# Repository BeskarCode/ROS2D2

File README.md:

# ROS2D2

<picture>
  <source media="(prefers-color-scheme: dark)" srcset="media/ros2d2-logo-dark.png">
  
</picture>

> **Work in progress: everything here is still being tested.** Parts run in the simulator and on
> the bench; testing on the droid is under way. Not yet a recipe to follow on your own droid.

A ROS 2 brain for an R2-D2 that runs ShadowMD. It works with [ShadowMD Lite](https://github.com/BeskarCode/ShadowMDLite) or with the classic Shadow MD ([SHADOW_MD_EEBEL](https://github.com/BeskarCode/SHADOW_MD_EEBEL)); in both it is enabled with `ENABLE_ROS2D2`, off by default. A Raspberry Pi 4 sits on top of the
droid's Arduino Mega: the Pi handles the senses (cameras, voice, later a lidar) and
decides what to do, and the Mega keeps driving the motors, sounds and lights.

The controller always wins: touch the stick and control is back with you at once.
The Mega also stops the dome if the Pi goes quiet for 300 ms.

First demo: the dome turns to look at you. It is the [DomeTracker](https://github.com/BeskarCode/DomeTracker)
proof of concept, split into ROS 2 nodes.

```
 camera ──image_raw──> face detector ──faces──> dome tracker ──/dome/speed_cmd──> Mega bridge ──DM:<speed>──> Mega
```

## The web console

ROS2D2 has its own web console, served by the Pi (`http://<pi>:8080`), to watch and set up the droid
from any browser.
Everything it does, page by page: the **[user manual](MANUAL.md)** ([en castellano](MANUAL_es.md)); its
**Manual** button opens it at the page you are on.

**Navigation**: the floor around R2 seen from above with the lidar's points, the free circle and
each sensor's beam, R2 in 3D, and every sensor's reading. Click the floor to send R2 there.

**Setup → Sensors**: where each sensor sits and what it covers. Drag a test object round R2 and the
sensors that would see it light up; switch a sensor that gives false readings to *ignored* in one
click; set the lidar (motor, scan mode, blind sectors) and read what it says about itself.

**Setup → Modes**: each automatic mode starts with its own controller combination. What each one does:

| | |
|---|---|
|  |  |
|  |  |

## Hardware

What ROS2D2 adds to a ShadowMD droid, how it connects and the bill of materials: [HARDWARE.md](HARDWARE.md).

## Packages (`ros2_ws/src`)

| Package | Node | What it does |
|---|---|---|
| `r2_camera` | `camera_node` | USB or network (ESP32-CAM) camera, one instance per camera |
| `r2_vision` | `face_detector` | OpenCV YuNet face detector, closest face first |
| `r2_dome_tracker` | `dome_tracker` | Dome speed from the face position (control law tuned on the droid) |
| `r2_shadow_bridge` | `mega_bridge`, `foot_calibrate` | The only node that talks to the Mega over USB serial; the feet move only in autonomous mode (PS + L2 on the foot controller), the dome only with face tracking on (PS + L2 on the dome controller); the two are independent |
| `r2_imu` | `imu_node` | MPU6050 gyro and accelerometer over I2C, plus a Madgwick filter |
| `r2_sensors` | `sensor_tf`, `fake_lidar`, `scan_crop`, `lidar_motor` | Where the lidar and the distance sensors (VL53L0X, HC-SR04 on a Pico) sit, from `sensors.yaml` (edited in the web console: Setup → Sensors), on `/tf_static`; the lidar's `/scan` cut to what the droid does not hide; a pretend lidar with `lidar:=sim` |
| `r2_pico_bridge` | `pico_bridge`, `fake_pico` | Talks to the Raspberry Pi Pico that reads the distance sensors (`firmware/r2_pico_sensors`, on `/dev/r2-pico`): sends it the sensors and pins from `sensors.yaml` (again on every save), publishes `/range/<name>` for each sensor that answers and `/pico/state` (JSON) for the console. Not started with `sim:=true` (the simulator has its own `/range`) or `pico:=false`. Flash the Pico from the PC with `firmware/r2_pico_sensors/flash.sh` |
| `r2_web` | `web_console` | Web console on port 8080: cameras, faces, 3D dome, camera and sensor setup |
| `r2_bringup` | | Launch files: `ros2 launch r2_bringup dome_tracker.launch.py` |

## Raspberry Pi setup

Ubuntu Server 24.04 (64-bit) on a Pi 4, then:

```
sudo bash setup/setup_r2_brain.sh
```

It installs ROS 2 Jazzy, the camera and web tools, and the serial port permissions.
Takes 1.5 to 2.5 hours, mostly waiting on the microSD: use a fast A2 card.

From then on, to put the code of this computer on the Pi (Git Bash on the computer):

```
PI=<your-user>@<pi-address> setup/deploy.sh              # every package, or name some: r2_web r2_nav
```

It copies `ros2_ws/src`, rebuilds what it copied and writes `~/r2_ws/VERSION` (the commit),
which the web console shows in Setup -> System.

So that the console can check GitHub for new Pico firmware and flash it (Setup -> System ->
Pico firmware), once, on the Pi as the ROS2D2 user (not root):

```
setup/install_pico_toolchain.sh
```

It installs `arduino-cli` with the Pico core and libraries (about 2 GB, a few minutes), a copy
of the repo's `firmware/` in `~/ros2d2-firmware`, and `/usr/local/sbin/r2-pico-flash` with a
sudoers rule for that one script. A build on a Pi 4 takes 2 to 3 minutes.

### Naming the USB devices (lidar, Mega, Pico)

ROS2D2 finds its USB serial devices by fixed names: `/dev/r2-mega`, `/dev/r2-lidar` and
`/dev/r2-pico`. Genuine Megas and the Pico get theirs on their own. The RPLIDAR C1's USB
adapter uses a common chip (CP210x) that a Mega clone can also have, so it is named by its
serial number, once:

```
./setup/r2-usb-names.sh                       # lists the ports: plug in the lidar and find its line
sudo ./setup/r2-usb-names.sh r2-lidar ttyUSB0 # the device now on ttyUSB0 is /dev/r2-lidar from now on
sudo systemctl restart r2d2
```

With `/dev/r2-lidar` present, the lidar starts with the droid (`lidar:=auto`) and its scan
shows in the web console (Sensors and Navigation). Its driver runs in its own service,
`r2d2-lidar` (installed by `setup_r2_brain.sh`): udev starts it when the lidar is plugged in and
systemd stops it when it is unplugged, so the lidar comes back on its own after being unplugged,
without restarting the rest (`journalctl -u r2d2-lidar -f` to watch it). If `/etc/default/r2d2` still has
`sim:=true` or `lidar:=sim` in `R2D2_ARGS` (from testing without the lidar), take it out:
in the simulation the real lidar is not started. The same command names a Mega clone
(`r2-mega`).

### Ignoring a sensor (Setup → Sensors)

Each sensor's card has an in use / ignored switch (next to its eye). A sensor that gives false
readings can be ignored at once: navigation and follow stop using it within a second or two, but it
keeps measuring and its card still shows its reading, greyed, so you can see when it is back and
switch it on again. The switch saves only that sensor's `enabled` line in `sensors.yaml` (any other
change in the cards still waits for Save); it stays ignored after a restart. Ignoring the last thing
that looks ahead shows a warning: with nothing ahead, navigation does not move. An ignored lidar
keeps spinning as its motor setting says, but the modes treat R2 as having no lidar.

### The lidar's settings (Setup → Sensors)

The lidar's card in the web console also sets the lidar itself, kept in `sensors.yaml`:

- **motor**: `always` (the default), `with_modes` (spins only while an automatic mode is on; a mode
  that starts waits up to 5 s for the first scan, then drives as without a lidar; the motor stops
  5 s after the last mode goes off) or `off`. The `lidar_motor` node does it with the driver's
  `start_motor` / `stop_motor`.
- **scan mode**: the modes the lidar says it has (a C1: Standard, 16 m; DenseBoost, 40 m).
  Changing it, or **upside down**, restarts only `r2d2-lidar`.
- **blind sectors**: angles of the lidar's own view `scan_crop` ignores (R2's leg); they mirror with
  upside down, and show shaded on the top-down map.
- the lidar's **info**: model, firmware, hardware, health, mode, turns per second and points per turn.

The speed of a C1's motor cannot be changed: asked for 480, 900 or 1200 rpm it keeps turning at
about 10.5 turns per second. The info and the mode list come from `/lidar/info`, which our fork of
`sllidar_ros2` publishes (`SLLIDAR_COMMIT` in `setup/setup_r2_brain.sh`); without it the card shows
`unknown` and the two C1 modes. Our fork also makes `start_motor` resume the configured scan mode
and `stop_motor` really stop a C1.

## Test bench on a PC (Docker)

The same ROS 2 Jazzy in a container, with a video file or a webcam instead of the
dome camera and a fake Mega (a socat pty pair) instead of the real one:

```
docker build -t ros2d2-dev docker
docker run --rm -v <this folder>:/r2 -v <video folder>:/media ros2d2-dev \
    bash /r2/docker/bench.sh /media/video.mp4 25
```

With a webcam on Windows, `python docker/webcam_mjpeg.py 1` serves it as an MJPEG
stream (the same format as an ESP32-CAM) and opens a test page at
<http://localhost:8081/> with Start and Stop buttons. See the top of `docker/bench.sh`.

## Credits

ROS2D2 is created by **NandoMadrid** ([R2-D2 by NandoMadrid](https://www.astromechspain.com/droides/r2-d2-nandomadrid/)), member of [Astromech Spain](https://www.astromechspain.com).

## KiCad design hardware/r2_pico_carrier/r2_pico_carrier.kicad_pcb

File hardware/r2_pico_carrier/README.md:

# R2 Pico carrier

*En castellano: [README_es.md](README_es.md)*

A carrier board for the **Raspberry Pi Pico 2** that reads R2's distance sensors (firmware:
`firmware/r2_pico_sensors`). It is ordered **already assembled**: you only plug in the Pico (with its
pins soldered facing down) and the sensor cables.

- 80 × 90 mm, 2 layers, 4 M3 holes in the corners.
- Arrives **assembled at the factory**: only the Pico and the display are missing.
- On the back: Astromech Spain's round logo, **ROS2D2**, **by NandoMadrid**, www.astromechspain.com.
- Schematic: [`renders/schematic.pdf`](renders/schematic.pdf). 3D view: [`renders/3d.png`](renders/3d.png).

## Connectors

Each connector has its pins **in the same order as the module**, so a straight female-female Dupont
cable goes directly, without crossing anything. Pin 1 is the one on the left (square pad).

| Connector | Pins (left → right) | For |
|---|---|---|
| **VL1 … VL4** | 3V3 · GND · SCL · SDA · — (GPIO1, free) · XSHUT | VL53L0X (GY-530) with a cable up to 1 m: all four go through the I2C repeater (PCA9517A) |
| **US1 … US5** | 5V · TRIG · ECHO · GND | HC-SR04. The ECHO divider (1 kΩ / 2 kΩ) is already on the board |
| **OLED** (J2, male header) | GND · VCC · SCL · SDA | 0.96" SSD1306/SSD1315 4-pin I2C display: soldered on top, lying flat, screen up |
| **+5V / GND** (terminal) | 5 V from the droid's supply | Powers the HC-SR04 and the Pico |
| **USB-C 5V** (J5, left edge) | power only | The same as the terminal, with any USB-C or USB-A→C charger (5 V) |
| **QWIIC** (J3, JST-SH 1 mm) | GND · 3V3 · SDA · SCL | Any Qwiic/STEMMA QT module at 3.3 V (IMU, more ToF, GPIO expander, ADC…) |
| **EXP** (J4, 2.54 header) | 5V · GND · 3V3 · SCL · SDA · RUN | Add-ons: the same I2C bus, 5 V and 3.3 V, and RUN (to GND resets the Pico) |
| **DISPLAY** | push button | Turns the display on and steps through the sensors |

With today's `sensors.yaml`: `tof_front_left` → VL1, `tof_front` → VL2, `tof_front_right` → VL3,
`tof_floor` → VL4, `sonar_front_left` → US1, `sonar_front_right` → US2, `sonar_rear` → US3. US4 and
US5 are for the two spare HC-SR04 (GP18/19 and GP20/21).

**Cable rule:** any VL53L0X on any VL, with a cable up to **1 m** (all four at once too: 4 × 1 m fit
with room to spare on the repeater's bus). The HC-SR04 take long cables on any US.

## Power

- **+5V / GND terminal** or **USB-C**: 5 V from the droid's supply or from any USB-C charger (the two
  5.1 kΩ resistors on CC ask it for the 5 V; there is no data). Each input has its own diode, so both
  can be connected at once without one feeding the other, and both go through the same resettable
  fuse (750 mA). The terminal's diode also protects against reversed polarity. The red LED next to
  the terminal (D4) says there are 5 V.
- **Connect the terminal with the Pico's USB unplugged, and check the polarity.** The diode only
  protects if the board has no other ground: with the USB plugged in, the Pi's ground is the board's
  ground too, and reversed wires would short through the USB cable, past both the fuse and the diode.
- The Pico's **USB** goes to the Pi 4 for data. The Pico works on the USB or on the terminal; the
  HC-SR04 **only on the terminal or the USB-C** (the LEDs and the display run on 3.3 V: they also work
  on the USB alone).

## Plugging in the Pico

With the **USB towards the top edge** (where it says USB) and pin 1 next to the "1". The wrong way
round, or one row off, **it can be damaged**: VSYS's 5 V would land on a GPIO or on GND. Look twice
before powering it.

## Display and LEDs

Off until you press **DISPLAY**: the first press, the logo; the next, the last sensor seen; each
press, the next one. After 30 s without a press everything goes off.

One red 0603 LED per connector, next to it, each on its own GPIO (GPIO → 1 kΩ → LED → GND, ~1.3 mA).
The states are told by blinking:

| LED | Means |
|---|---|
| steady on | that sensor is measuring |
| blinking (0.4 s) | configured but not answering |
| off | no sensor configured on that connector |
| short flash every 2 s, all of them | waiting for the Pi to send the setup |
| a short inverted blink every second | it is the connector on the display |

| Connector | VL1 | VL2 | VL3 | VL4 | US1 | US2 | US3 | US4 | US5 |
|---|---|---|---|---|---|---|---|---|---|
| LED GPIO | GP28 | GP27 | GP22 | GP9 | GP0 | GP1 | GP6 | GP7 | GP8 |

That is why those GPIOs are reserved: the firmware and the console do not offer them for sensors.

## Add-ons

The Pico has no free GPIOs left, so anything added goes over **I2C**: the **QWIIC** connector (a
4-wire JST-SH cable, no soldering) or the **EXP** header. Both are on the Pico's short bus (GP16
SDA, GP17 SCL, 4.7 kΩ pull-ups on the board), together with VL1, VL2 and the display: do not use
addresses 0x29 (VL53L0X) or 0x3C (display), and keep cables short (< 50 cm). An I2C expander
(PCF8574, MCP23017…) gives plenty of GPIOs if needed. Do not connect other I2C repeaters or
accelerators (PCA9515/9517, LTC4311…) on QWIIC/EXP: U1's B side cannot share a bus with them.

## Ordering it

> **Tested and working** (November 2026): the boards JLCPCB assembled for us read the VL53L0X and
> the HC-SR04, and the LEDs, the display and its button work.

The files to make it (Gerber, BOM, placement and the board design) are not published in this repo.
The schematic ([`renders/schematic.pdf`](renders/schematic.pdf)) and the renders are here so you can
see how it is wired. Without the board, the sensors can be wired to the Pico by hand:
[`firmware/r2_pico_sensors/wiring.svg`](../../firmware/r2_pico_sensors/wiring.svg).

## What to buy separately

- 0.96" OLED display, **128×64 SSD1306 (or SSD1315) 4-pin I2C**, in the order **GND-VCC-SCL-SDA**
  (some come as VCC-GND: check it), **without the header soldered** (it usually comes loose). J2
  already comes with 4 male pins: put the display on them, screen up and lying on its outline,
  resting on the header's plastic (2.5 mm), solder the 4 pins from the top and cut what is left. If
  you like, also fix it with 4 M2 2.5 mm spacers in H5-H8. Once soldered it does not come off easily.
- Female-female Dupont cables.
- 1×20 male pin headers to solder to your Pico 2 (facing down), if it has none.

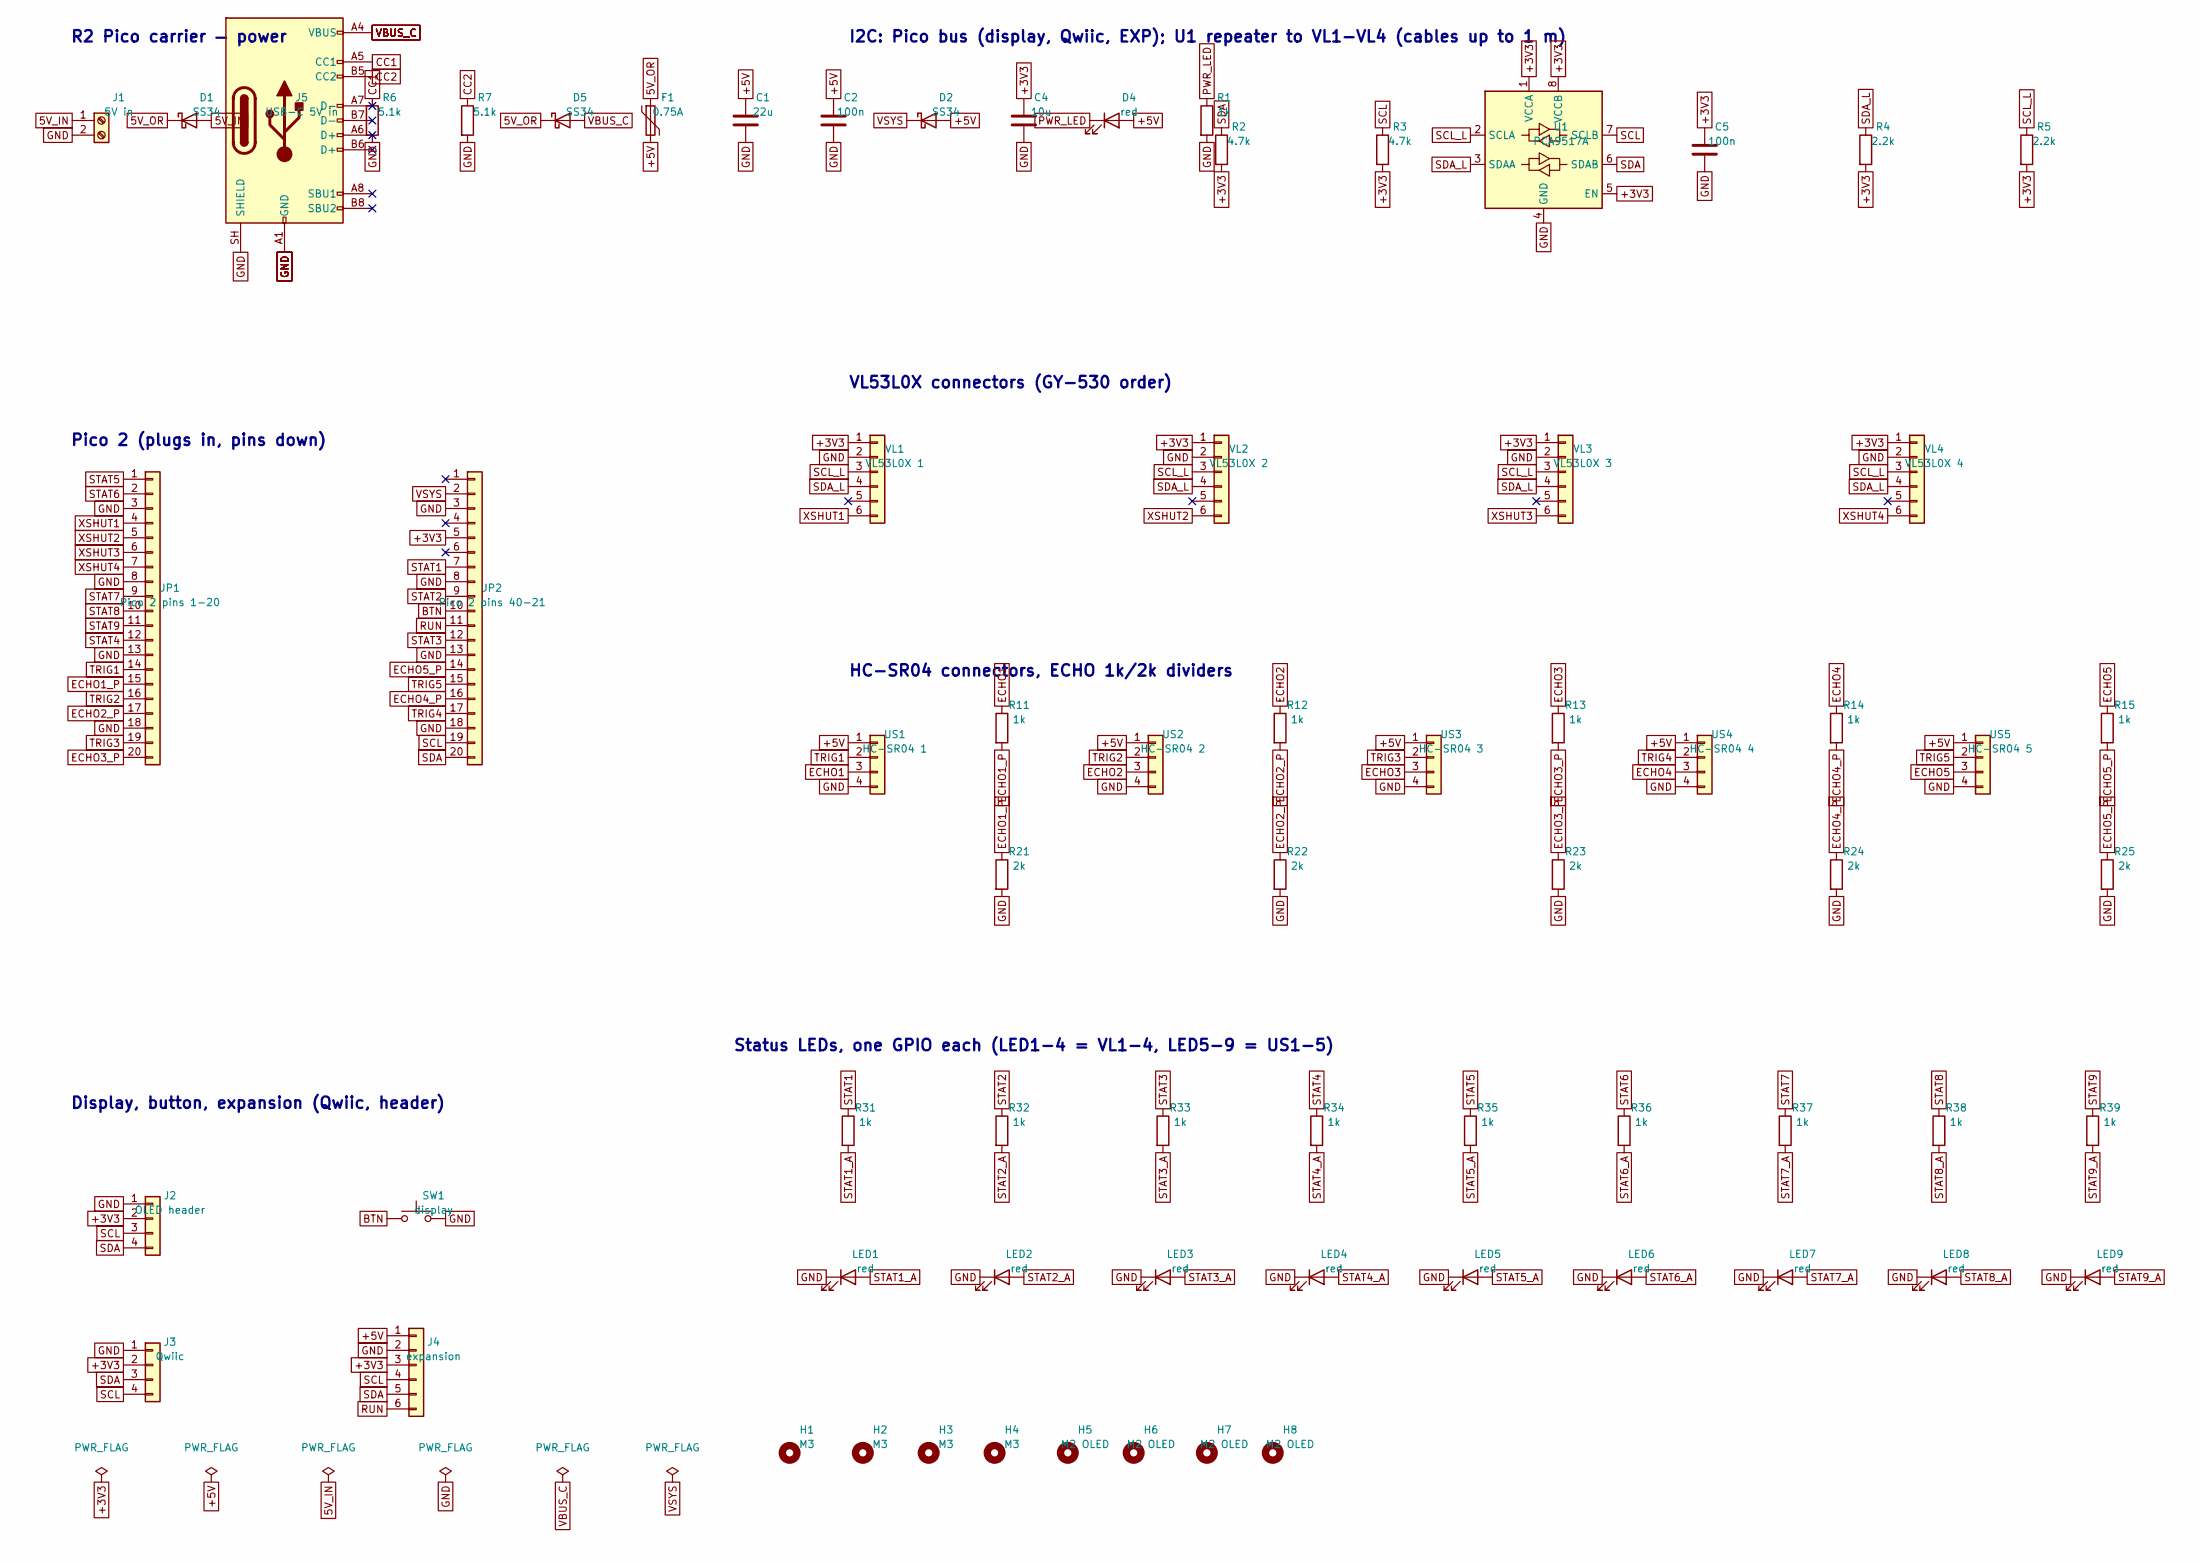
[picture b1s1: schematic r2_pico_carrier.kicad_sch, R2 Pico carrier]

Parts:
C1: 22u; C_0805_2012Metric; LCSC C45783
C2, C5: 100n; C_0603_1608Metric; LCSC C14663
C4: 10u; C_0805_2012Metric; LCSC C15850
D1, D2, D5: SS34; D_SMA; LCSC C8678
D4: red; LED_0603_1608Metric; LCSC C2286
F1: 0.75A; Fuse_1206_3216Metric; LCSC C976305
H1, H2, H3, H4: M3; MountingHole_3.2mm_M3
H5, H6, H7, H8: M2 OLED; MountingHole_2.2mm_M2
J1: 5V in; TerminalBlock_Phoenix_MKDS-1,5-2-5.08_1x02_P5.08mm_Horizont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; LCSC C474952
J2: OLED header; PinHeader_1x04_P2.54mm_Vertical; LCSC C2691448
J3: Qwiic; JST_SH_BM04B-SRSS-TB_1x04-1MP_P1.00mm_Vertical; LCSC C160390
J4: expansion; PinHeader_1x06_P2.54mm_Vertical; LCSC C37208
J5: USB-C 5V in; USB_C_Receptacle_HRO_TYPE-C-31-M-12; LCSC C165948
JP1: Pico 2 pins 1-20; PinSocket_1x20_P2.54mm_Vertical; LCSC C2905423
JP2: Pico 2 pins 40-21; PinSocket_1x20_P2.54mm_Vertical; LCSC C2905423
LED1, LED2, LED3, LED4, LED5, LED6, LED7, LED8, LED9: red; LED_0603_1608Metric; LCSC C2286
R1, R11, R12, R13, R14, R15, R31, R32, R33, R34, R35, R36, R37, R38, R39: 1k; R_0603_1608Metric; LCSC C21190
R2, R3: 4.7k; R_0603_1608Metric; LCSC C23162
R4, R5: 2.2k; R_0603_1608Metric; LCSC C4190
R6, R7: 5.1k; R_0603_1608Metric; LCSC C23186
R21, R22, R23, R24, R25: 2k; R_0603_1608Metric; LCSC C22975
SW1: display; SW_Push_1P1T_XKB_TS-1187A; LCSC C318884
U1: PCA9517A; VSSOP-8_3x3mm_P0.65mm; LCSC C80799
US1: HC-SR04 1; PinHeader_1x04_P2.54mm_Vertical; LCSC C2691448
US2: HC-SR04 2; PinHeader_1x04_P2.54mm_Vertical; LCSC C2691448
US3: HC-SR04 3; PinHeader_1x04_P2.54mm_Vertical; LCSC C2691448
US4: HC-SR04 4; PinHeader_1x04_P2.54mm_Vertical; LCSC C2691448
US5: HC-SR04 5; PinHeader_1x04_P2.54mm_Vertical; LCSC C2691448
VL1: VL53L0X 1; PinHeader_1x06_P2.54mm_Vertical; LCSC C37208
VL2: VL53L0X 2; PinHeader_1x06_P2.54mm_Vertical; LCSC C37208
VL3: VL53L0X 3; PinHeader_1x06_P2.54mm_Vertical; LCSC C37208
VL4: VL53L0X 4; PinHeader_1x06_P2.54mm_Vertical; LCSC C37208

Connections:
5V_IN: D1.2 (A), J1.1
5V_OR: D1.1 (K), D5.1 (K), F1.1
+3V3: C4.1, C5.1, J2.2, J3.2, J4.3, JP2.5, R2.2, R3.2, R4.2, R5.2, U1.1 (VCCA), U1.5 (EN), U1.8 (VCCB), VL1.1, VL2.1, VL3.1, VL4.1
+5V: C1.1, C2.1, D2.2 (A), D4.2 (A), F1.2, J4.1, US1.1, US2.1, US3.1, US4.1, US5.1
BTN: JP2.10, SW1.1
CC1: J5.A5 (CC1), R6.1
CC2: J5.B5 (CC2), R7.1
ECHO1: R11.1, US1.3
ECHO1_P: JP1.15, R11.2, R21.1
ECHO2: R12.1, US2.3
ECHO2_P: JP1.17, R12.2, R22.1
ECHO3: R13.1, US3.3
ECHO3_P: JP1.20, R13.2, R23.1
ECHO4: R14.1, US4.3
ECHO4_P: JP2.16, R14.2, R24.1
ECHO5: R15.1, US5.3
ECHO5_P: JP2.14, R15.2, R25.1
GND: C1.2, C2.2, C4.2, C5.2, J1.2, J2.1, J3.1, J4.2, J5.A1 (GND), J5.A12 (GND), J5.B1 (GND), J5.B12 (GND), J5.SH (SHIELD), JP1.3, JP1.8, JP1.13, JP1.18, JP2.3, JP2.8, JP2.13, JP2.18, LED1.1 (K), LED2.1 (K), LED3.1 (K), LED4.1 (K), LED5.1 (K), LED6.1 (K), LED7.1 (K), LED8.1 (K), LED9.1 (K), R1.2, R6.2, R7.2, R21.2, R22.2, R23.2, R24.2, R25.2, SW1.2, U1.4 (GND), US1.4, US2.4, US3.4, US4.4, US5.4, VL1.2, VL2.2, VL3.2, VL4.2
PWR_LED: D4.1 (K), R1.1
RUN: J4.6, JP2.11
SCL: J2.3, J3.4, J4.4, JP2.19, R3.1, U1.7 (SCLB)
SCL_L: R5.1, U1.2 (SCLA), VL1.3, VL2.3, VL3.3, VL4.3
SDA: J2.4, J3.3, J4.5, JP2.20, R2.1, U1.6 (SDAB)
SDA_L: R4.1, U1.3 (SDAA), VL1.4, VL2.4, VL3.4, VL4.4
STAT1: JP2.7, R31.1
STAT1_A: LED1.2 (A), R31.2
STAT2: JP2.9, R32.1
STAT2_A: LED2.2 (A), R32.2
STAT3: JP2.12, R33.1
STAT3_A: LED3.2 (A), R33.2
STAT4: JP1.12, R34.1
STAT4_A: LED4.2 (A), R34.2
STAT5: JP1.1, R35.1
STAT5_A: LED5.2 (A), R35.2
STAT6: JP1.2, R36.1
STAT6_A: LED6.2 (A), R36.2
STAT7: JP1.9, R37.1
STAT7_A: LED7.2 (A), R37.2
STAT8: JP1.10, R38.1
STAT8_A: LED8.2 (A), R38.2
STAT9: JP1.11, R39.1
STAT9_A: LED9.2 (A), R39.2
TRIG1: JP1.14, US1.2
TRIG2: JP1.16, US2.2
TRIG3: JP1.19, US3.2
TRIG4: JP2.17, US4.2
TRIG5: JP2.15, US5.2
VBUS_C: D5.2 (A), J5.A4 (VBUS), J5.A9 (VBUS), J5.B4 (VBUS), J5.B9 (VBUS)
VSYS: D2.1 (K), JP2.2
XSHUT1: JP1.4, VL1.6
XSHUT2: JP1.5, VL2.6
XSHUT3: JP1.6, VL3.6
XSHUT4: JP1.7, VL4.6

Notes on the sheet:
R2 Pico carrier — power
Pico 2 (plugs in, pins down)
I2C: Pico bus (display, Qwiic, EXP); U1 repeater to VL1-VL4 (cables up to 1 m)
VL53L0X connectors (GY-530 order)
HC-SR04 connectors, ECHO 1k/2k dividers
Status LEDs, one GPIO each (LED1-4 = VL1-4, LED5-9 = US1-5)
Display, button, expansion (Qwiic, header)

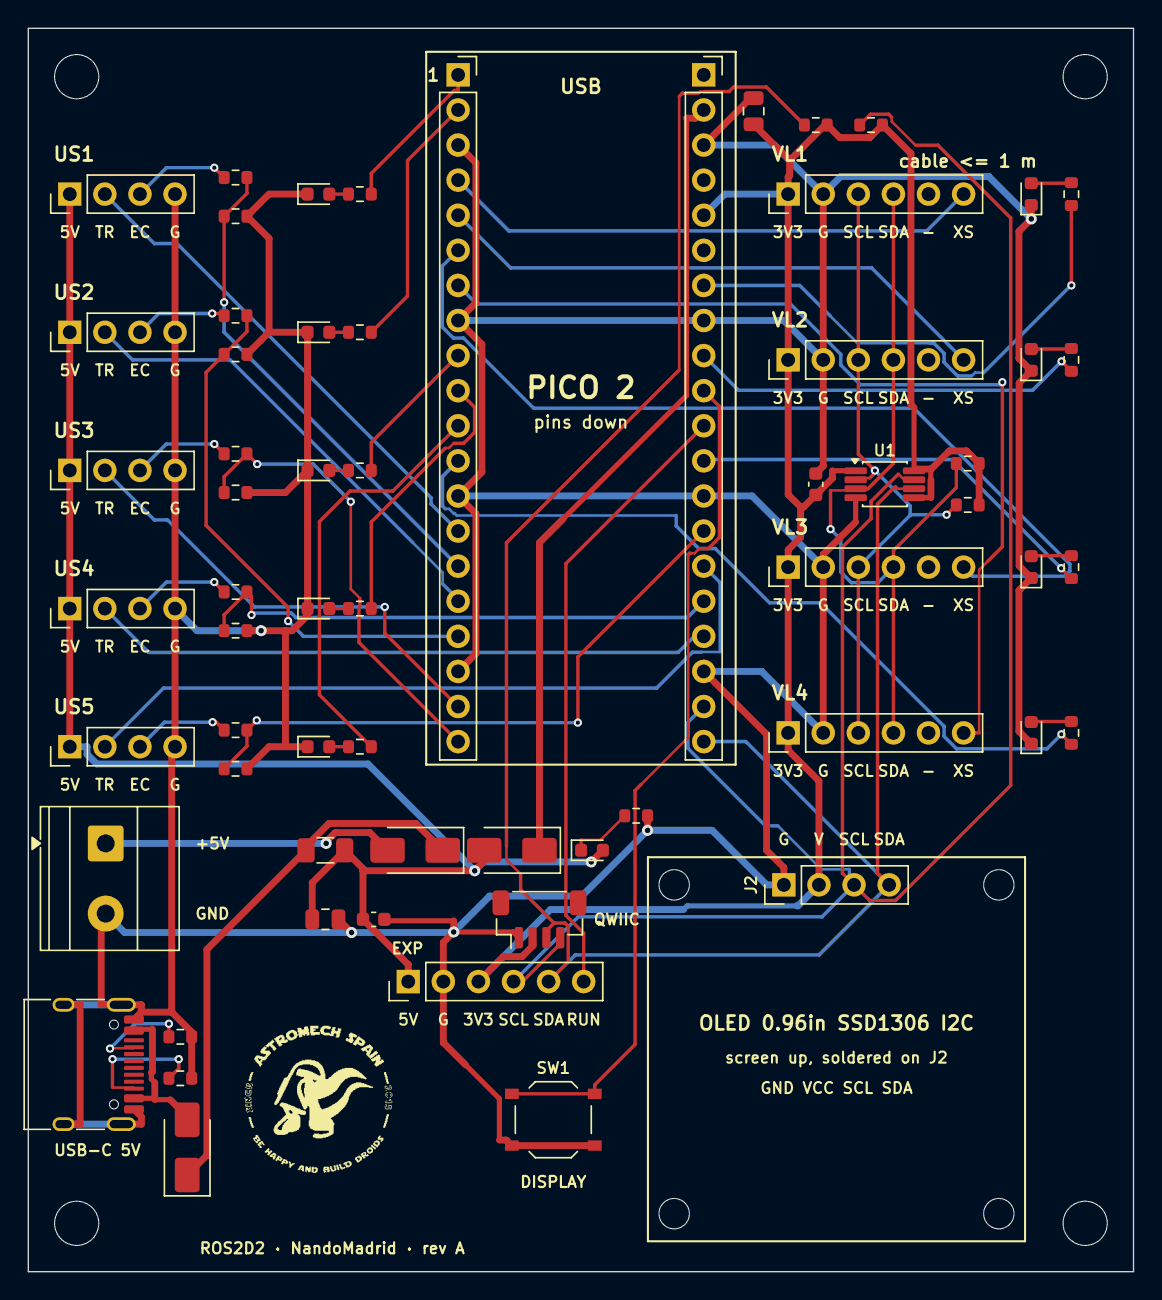
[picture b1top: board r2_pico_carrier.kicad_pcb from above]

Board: 2 copper layers, 80.0 x 90.0 mm, 70 parts (0 on the bottom side), 53 nets.

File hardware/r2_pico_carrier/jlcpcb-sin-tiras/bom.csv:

Comment,Designator,Footprint,LCSC Part #
22u,C1,C_0805_2012Metric,C45783
100n,"C2,C5",C_0603_1608Metric,C14663
10u,C4,C_0805_2012Metric,C15850
SS34,"D1,D2,D5",D_SMA,C8678
red,"D4,LED1,LED2,LED3,LED4,LED5,LED6,LED7,LED8,LED9",LED_0603_1608Metric,C2286
0.75A,F1,Fuse_1206_3216Metric,C976305
5V in,J1,"TerminalBlock_Phoenix_MKDS-1,5-2-5.08_1x02_P5.08mm_Horizontal",C474952
Qwiic,J3,JST_SH_BM04B-SRSS-TB_1x04-1MP_P1.00mm_Vertical,C160390
USB-C 5V in,J5,USB_C_Receptacle_HRO_TYPE-C-31-M-12,C165948
Pico 2 pins 1-20,"JP1,JP2",PinSocket_1x20_P2.54mm_Vertical,C2905423
1k,"R1,R11,R12,R13,R14,R15,R31,R32,R33,R34,R35,R36,R37,R38,R39",R_0603_1608Metric,C21190
4.7k,"R2,R3",R_0603_1608Metric,C23162
2.2k,"R4,R5",R_0603_1608Metric,C4190
5.1k,"R6,R7",R_0603_1608Metric,C23186
2k,"R21,R22,R23,R24,R25",R_0603_1608Metric,C22975
display,SW1,SW_Push_1P1T_XKB_TS-1187A,C318884
PCA9517A,U1,VSSOP-8_3x3mm_P0.65mm,C80799
